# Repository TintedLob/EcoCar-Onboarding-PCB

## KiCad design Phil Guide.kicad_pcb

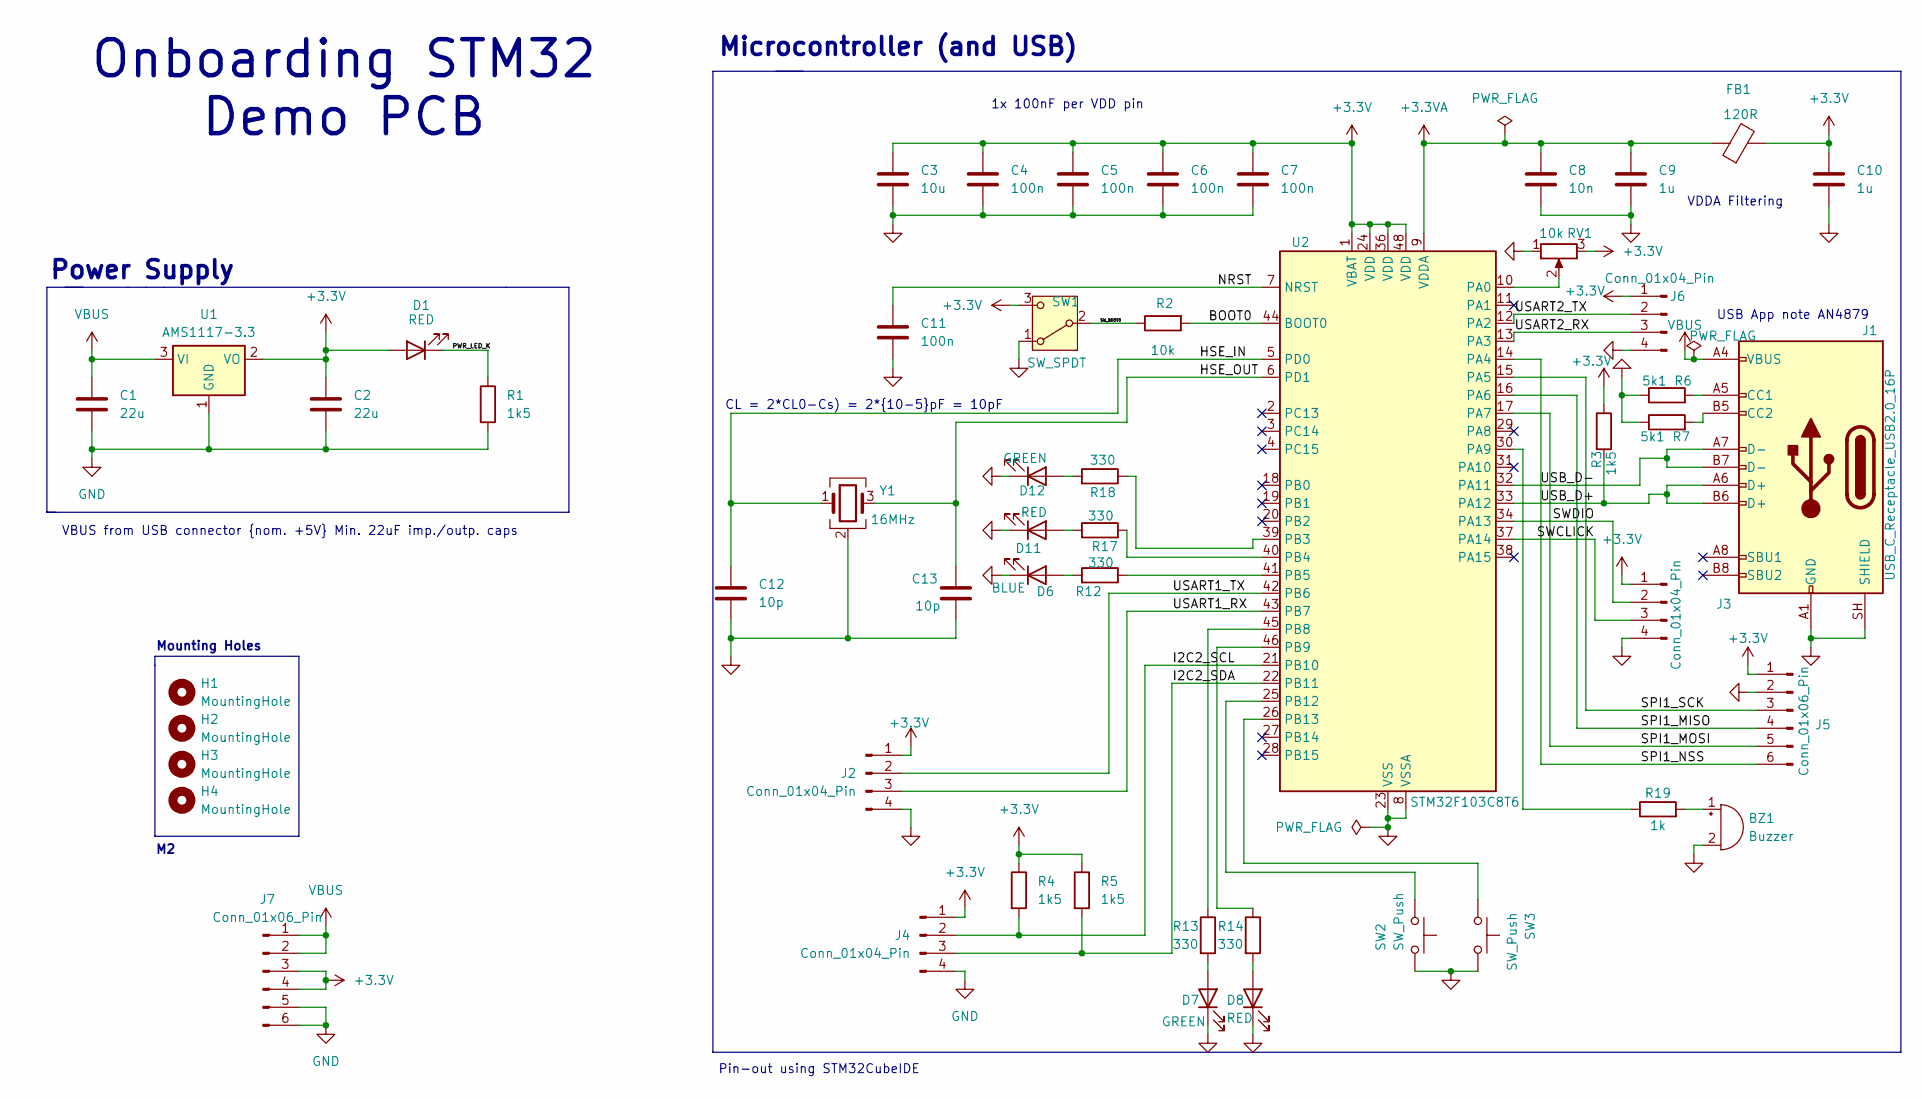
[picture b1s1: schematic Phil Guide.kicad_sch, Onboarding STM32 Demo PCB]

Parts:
BZ1: Buzzer; Buzzer_12x9.5RM7.6
C1, C2: 22u; C_0805_2012Metric
C3: 10u; C_0603_1608Metric
C4, C5, C6, C7, C11: 100n; C_0603_1608Metric
C8: 10n; C_0603_1608Metric
C9, C10: 1u; C_0603_1608Metric
C12, C13: 10p; C_0603_1608Metric
D1, D8, D11: RED; LED_0603_1608Metric
D6: BLUE; LED_0603_1608Metric
D7, D12: GREEN; LED_0603_1608Metric
FB1: 120R; L_0603_1608Metric
H1, H2, H3, H4: MountingHole; MountingHole_2.2mm_M2
J1: USB_C_Receptacle_USB2.0_16P; USB_C_Receptacle_GCT_USB4105-xx-A_16P_TopMnt_Horizontal
J2, J3, J4, J6: Conn_01x04_Pin; PinHeader_1x04_P2.54mm_Vertical
J5, J7: Conn_01x06_Pin; PinHeader_1x06_P2.54mm_Vertical
R1, R3, R4, R5: 1k5; R_0603_1608Metric
R2: 10k; R_0603_1608Metric
R6, R7: 5k1; R_0603_1608Metric
R12, R13, R14, R17, R18: 330; R_0603_1608Metric
R19: 1k; R_0603_1608Metric
RV1: 10k; Potentiometer_Bourns_3296W_Vertical
SW1: SW_SPDT; SW_SPDT_PCM12
SW2, SW3: SW_Push; SW_PUSH_6mm
U1: AMS1117-3.3; SOT-223-3_TabPin2
U2: STM32F103C8T6; LQFP-48_7x7mm_P0.5mm
Y1: 16MHz; Crystal_SMD_3225-4Pin_3.2x2.5mm

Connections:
+3.3V: C2.1, C3.1, C4.1, C5.1, C6.1, C7.1, C10.1, D1.2 (A), FB1.2, J2.1, J3.1, J4.1, J5.1, J6.1, J7.3, J7.4, R3.1, R4.1, R5.1, RV1.3, SW1.3 (C), U1.2 (VO), U2.1 (VBAT), U2.24 (VDD), U2.36 (VDD), U2.48 (VDD)
+3.3VA: C8.1, C9.1, FB1.1, U2.9 (VDDA)
/BOOT0: R2.2, U2.44 (BOOT0)
/HSE_IN: C12.1, U2.5 (PD0), Y1.1
/HSE_OUT: C13.1, U2.6 (PD1), Y1.3
/I2C2_SCL: J4.2, R4.2, U2.21 (PB10)
/I2C2_SDA: J4.3, R5.2, U2.22 (PB11)
/NRST: C11.1, U2.7 (NRST)
/PWR_LED_K: D1.1 (K), R1.1
/SPI1_MISO: J5.4, U2.16 (PA6)
/SPI1_MOSI: J5.5, U2.17 (PA7)
/SPI1_NSS: J5.6, U2.14 (PA4)
/SPI1_SCK: J5.3, U2.15 (PA5)
/SWCLICK: J3.3, U2.37 (PA14)
/SWDIO: J3.2, U2.34 (PA13)
/SW_BOOT0: R2.1, SW1.2 (B)
/USART1_RX: J2.3, U2.43 (PB7)
/USART1_TX: J2.2, U2.42 (PB6)
/USART2_RX: J6.3, U2.13 (PA3)
/USART2_TX: J6.2, U2.12 (PA2)
/USB_D+: J1.A6 (D+), J1.B6 (D+), R3.2, U2.33 (PA12)
/USB_D-: J1.A7 (D-), J1.B7 (D-), U2.32 (PA11)
GND: BZ1.2 (-), C1.2, C2.2, C3.2, C4.2, C5.2, C6.2, C7.2, C8.2, C9.2, C10.2, C11.2, C12.2, C13.2, D6.1 (K), D7.1 (K), D8.1 (K), D11.1 (K), D12.1 (K), J1.A1 (GND), J1.A12 (GND), J1.B1 (GND), J1.B12 (GND), J1.SH (SHIELD), J2.4, J3.4, J4.4, J5.2, J6.4, J7.5, J7.6, R1.2, R6.1, R7.1, RV1.1, SW1.1 (A), SW2.2, SW3.2, U1.1 (GND), U2.8 (VSSA), U2.23 (VSS), U2.35 (VSS), U2.47 (VSS), Y1.2 (G), Y1.4 (G); also elsewhere on the board
unnamed: BZ1.1 (+), R19.2
unnamed: D6.2 (A), R12.2
unnamed: D7.2 (A), R13.2
unnamed: D8.2 (A), R14.2
unnamed: D11.2 (A), R17.2
unnamed: D12.2 (A), R18.2
unnamed: J1.A5 (CC1), R6.2
unnamed: J1.B5 (CC2), R7.2
unnamed: RV1.2, U2.10 (PA0)
unnamed: R19.1, U2.30 (PA9)
unnamed: R18.1, U2.39 (PB3)
unnamed: R17.1, U2.40 (PB4)
unnamed: R12.1, U2.41 (PB5)
unnamed: R13.1, U2.45 (PB8)
unnamed: R14.1, U2.46 (PB9)
unnamed: SW2.1, U2.25 (PB12)
unnamed: SW3.1, U2.26 (PB13)
VBUS: C1.1, J1.A4 (VBUS), J1.A9 (VBUS), J1.B4 (VBUS), J1.B9 (VBUS), J7.1, J7.2, U1.3 (VI)

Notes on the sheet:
USB App note AN4879
Mounting Holes
Pin-out using STM32CubeIDE
Power Supply
VBUS from USB connector {nom. +5V} Min. 22uF imp./outp. caps
Onboarding STM32 Demo PCB
VDDA Filtering
CL = 2*CL0-Cs) = 2*{10-5}pF = 10pF
Microcontroller (and USB)
1x 100nF per VDD pin

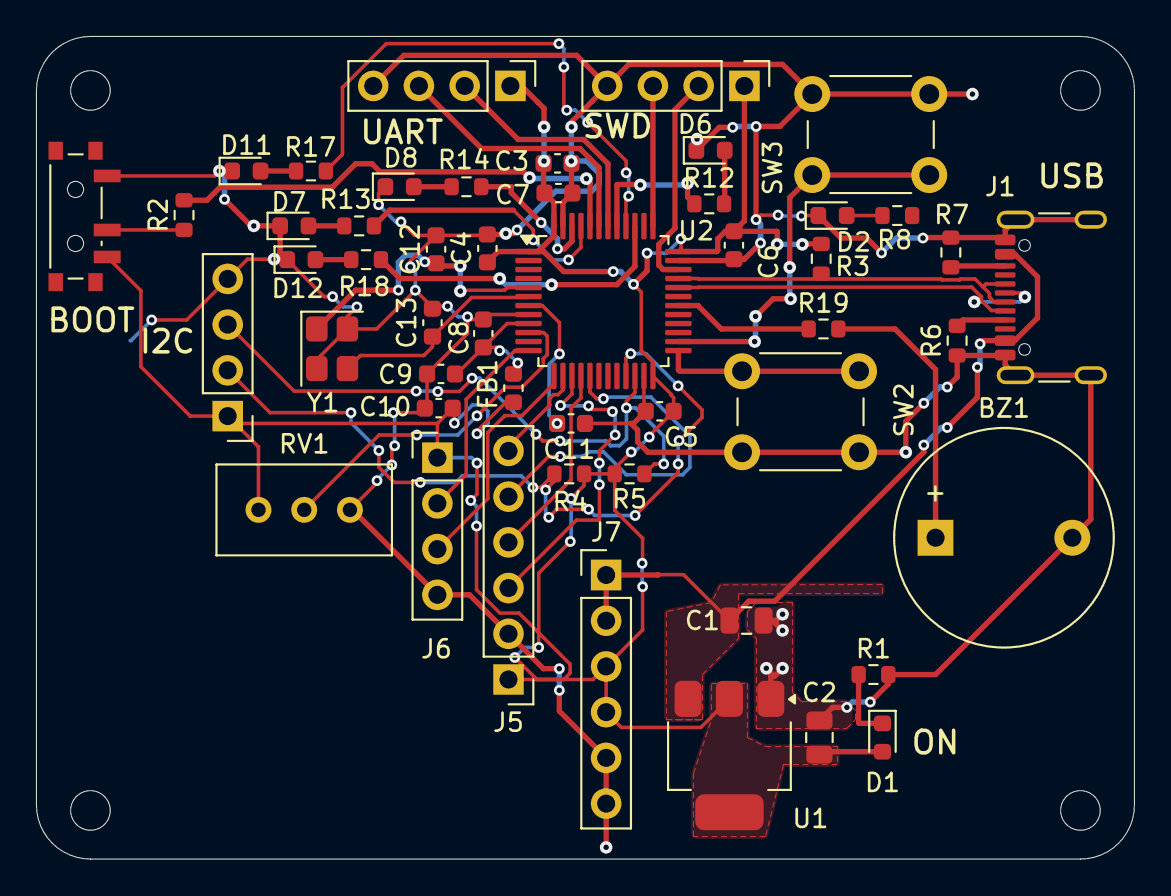
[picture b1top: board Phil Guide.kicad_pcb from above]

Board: 2 copper layers, 61.0 x 45.7 mm, 54 parts (0 on the bottom side), 42 nets.

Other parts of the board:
D2: WHITE; LED_0603_1608Metric
R8: 330; R_0603_1608Metric

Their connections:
GND: D2.1 (K); also elsewhere on the board
unnamed: D2.2 (A), R8.2
